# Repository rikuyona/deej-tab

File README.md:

# deej-tab

物理スライダーで、Windows / Mac のアプリごとの音量と **ブラウザ（Chrome・Edge など）のタブごとの音量** を操作する自作ミキサーです。
[deej](https://github.com/omriharel/deej) を元に、PC アプリ・ブラウザの拡張機能・LED 付きファームウェア・3D プリント用ケース（[MakerWorld](https://makerworld.com/models/3382344)）までまとめてあります。

<p align="center"><sub>完成イメージ（3D レンダリング）。スライダー 5 本・ノブ 1 つ、外形 126×126mm</sub></p>

- [できること](#できること) / [必要なもの](#必要なもの) / [セットアップ](#セットアップ) / [使い方](#使い方) / [困ったとき](#困ったとき) / [Mac 版について](#mac-版について) / [仕組み](#仕組み) / [開発](#開発)

## できること

- スライダー 5 本＋ノブ 1 つに、全体音量・マイク・アプリ（Discord・Spotify など）・**Chrome のタブ**・今使っているアプリ・ゲーム・OBS の音声ソースを割り当てる
- Chrome で開いた配信や動画を、タブごとに別のスライダーで調整（Alt+Shift+A でタブを割り当て）
- 日本語・英語の画面（English UI）
- 設定画面で割り当て・スライダーごとの最大音量（100% 超えも可。タブ・OBS のみ）・音量の変わり方を変更
- プロファイル（割り当て一式）の切り替え。アプリが前に来たら自動で切り替えも可
- 一時停止（ショートカットも可）。止めるとアプリの音量を元に戻す（全体の音量はそのまま）
- スライダーの LED で状態や音の大きさを表示。光り方は設定画面で選べる
- config.yaml は deej と互換

## 必要なもの

作り方は 2 通りあります。PC アプリ・拡張機能・ファームウェアはどちらも同じです。

| | 配線版 | 基板版 |
|---|---|---|
| 作り方 | スライダーごとに Nano まで線を引き回してハンダ付け | スライダー 5 本とノブを 1 枚の基板に載せ、Nano とはケーブル 3 本でつなぐ |
| 向いている人 | 基板を注文せず、部品だけで作りたい | 配線の手間を減らしたい（基板は JLCPCB などに注文） |
| 部品・作り方 | 下の [部品（配線版）](#部品配線版) と [配線（配線版）](#配線配線版) | 下の [部品（基板版）](#部品基板版) と [pcb/README.md](pcb/README.md) |
| ケース | [MakerWorld](https://makerworld.com/models/3382344) | [Releases](../../releases/tag/pcb-v0.1.0) の `deej-tab-pcb-0.1.0-case.zip`（[下](#4-ケースを印刷する任意)） |

### PC

- Windows 10 / 11、または macOS 14.2 以降の Apple シリコン（M1 以降）の Mac（Mac は [Mac 版について](#mac-版について) を参照）
- Chrome・Edge・Brave など Chromium のブラウザ（Chrome 116 相当以降。タブの音量を操作する場合）

### 部品（配線版）

| 部品 | 例 | 数 |
|---|---|---|
| マイコン | Arduino Nano 互換ボード（USB Type-C 版。ケースは Mini-USB の Nano には合いません） | 1 |
| スライダー | Bourns PTL60-15R0-103B2（60mm・10kΩ B カーブ・赤 LED 付き） | 5 |
| 回転ボリューム | 16mm 型 10kΩ B カーブ（SH16K4B103L20KCCI など。6mm ローレット軸 18 山・軸長 20mm・M7 取付ネジ・回り止め付き） | 1 |
| ノブ | 3D プリント（[MakerWorld](https://makerworld.com/models/3382344) のデータ）または市販の 6mm 軸用（ABS-28 など） | 1 |
| LED 用抵抗 | 180Ω〜1kΩ（1/4W・1/6W など。例：330Ω） | 5 |
| M2 皿ネジ | M2×4 程度（ケースにスライダーを固定。1 本につき 2 本） | 10 |

LED 用抵抗：スライダーの赤色 LED はデータシートで順方向電流 20mA・順方向電圧 1.8V（標準）と規定されているので、5V で 20mA 以下にするには (5V − 1.8V) ÷ 20mA ≒ 160Ω 以上が必要です。値が小さいほど明るくなります（330Ω で約 10mA）。

LED なしのスライダーでも動きます（LED の機能が使えないだけです）。

### 配線（配線版）

同じ名前の札どうしをつなぎます。5V と GND は全部の部品で共通なので、まとめて Nano の 5V・GND へつなぎます。

| 部品 | 端子 | つなぐ先 |
|---|---|---|
| スライダー 1〜5 | 1 | GND |
| | 3 | 5V |
| | 2（ワイパー） | A0〜A4 |
| | B（LED＋） | 抵抗 → D3 / D5 / D6 / D9 / D10 |
| | E（LED−） | GND |
| | L | つながない |
| 回転ボリューム | 両端 | 5V / GND |
| | 中央 | A5 |

D0 / D1 は USB シリアルに使うので空けておきます。

### 部品（基板版）

基板を発注・組み立てて、スライダー 5 本・ノブの値と LED が動くことを確かめてあります。部品はすべてスルーホールで、手でハンダ付けします。

| 部品 | 例 | 数 |
|---|---|---|
| 基板 | [Releases](../../releases) の `pcb-v0.1.0` のガーバーを JLCPCB などに注文（2 層・1.6mm・100×100mm 以内） | 1 |
| マイコン | Arduino Nano 互換ボード（USB Type-C 版） | 1 |
| スライダー | Bourns PTL60-15R0-103B2（配線版と同じ） | 5 |
| 回転ボリューム | 配線版と同じ SH16K4B103L20KCCI（端子の曲がりを伸ばして基板に挿す。[pcb/README.md](pcb/README.md#ボリュームの端子)） | 1 |
| LED 用抵抗 | 150Ω 1/4W | 5 |
| コンデンサー | 0.1µF（各スライダー・ノブのノイズ対策）・10µF（5V） | 6・1 |
| コネクター | JST ZH 横向き 3 ピン（S3B-ZR-3.4）1 個・6 ピン（S6B-ZR-3.4）2 個 | 3 |
| コード | ZH 相当のコネクター付きコード 3P 黒白赤（秋月 118272）1 本・6P(H)（秋月 105719）2 本 | 3 |
| M2 皿ネジ | M2×4（スライダーを天板に固定） | 10 |

型番・秋月の通販番号入りの一覧は `pcb-v0.1.0` の `deej-tab-pcb-0.1.0-bom.csv`、ケーブルの対応・組み立て・注文のしかたは [pcb/README.md](pcb/README.md) にあります。基板版は上の「配線（配線版）」の代わりに、pcb/README.md の「ケーブル」と「組み立て」を見てください。

## セットアップ

[Releases](../../releases) の最新版から、使う PC に合わせてダウンロードします。

| やること | Windows | Mac |
|---|---|---|
| [1. PC アプリを入れる](#1-pc-アプリを入れる) | `deej-tab-x.y.z-setup.exe` | `deej-tab-x.y.z-mac.dmg` |
| [2. ファームウェアを書き込む](#2-コントローラーにファームウェアを書き込む) | 設定画面から（ダウンロード不要） | 設定画面から（ダウンロード不要） |
| [3. ブラウザの拡張機能を入れる](#3-ブラウザの拡張機能を入れる)（タブの音量を変えるとき） | インストール済み（読み込むだけ） | `deej-tab-extension-x.y.z.zip` |
| [4. ケースを印刷する](#4-ケースを印刷する任意)（任意） | MakerWorld（基板版は `pcb-v0.1.0` の case.zip） | MakerWorld（基板版は `pcb-v0.1.0` の case.zip） |

うまくいかないときは [困ったとき](#困ったとき) を見てください。

### 1. PC アプリを入れる

**Windows**

1. `deej-tab-x.y.z-setup.exe` をダブルクリックする
   - 「Windows によって PC が保護されました」と出たら、「詳細情報」→「実行」を押す（コード署名をしていない個人の配布物なので出ます）
2. 「次へ」を押す（「Windows の起動時に自動で起動する」は初期設定でオン）
3. 最後に「完了」を押すと deej-tab が起動して、設定画面が開く

管理者の許可は要りません。`%LOCALAPPDATA%\Programs\deej-tab` に入り、スタートメニューに deej-tab が出ます。deej-tab は画面右下のタスクトレイに常駐します（アイコンは「^」の中に隠れていることがあります）。

**Mac**（Apple シリコン・macOS 14.2 以降）

1. `deej-tab-x.y.z-mac.dmg` を開き、`deej-tab.app` を隣の「Applications」へドラッグする。入れ終わったら、Finder のサイドバーの ⏏ で dmg を取り出す（dmg の中から起動しないでください。取り出すと消えます）
2. 初回は次の手順で起動する（Apple の公証を受けていないため、ダブルクリックだけでは開けません）
   - **最近の macOS（15 Sequoia 以降。26 Tahoe など）**：`deej-tab.app` をダブルクリックし、「開いていません」と出たら「完了」を押す。システム設定 →「プライバシーとセキュリティ」を開き、下のほうの「セキュリティ」に出ている deej-tab の行で「このまま開く」を押す（パスワードを聞かれたら入力）
   - **macOS 14 Sonoma**：`deej-tab.app` を右クリック →「開く」→ 出てきた画面で「開く」
3. アプリごとの音量を初めて変えたときに「システムオーディオの録音」の許可を求められるので、許可する（音を受け取って音量をかけ直すだけで、録音・保存はしません）

deej-tab はメニューバーに常駐し、アイコンから設定画面を開けます。

### 2. コントローラーにファームウェアを書き込む

初めて使う Nano には、deej-tab の設定画面からファームウェアを書き込みます（Arduino IDE は要りません）。書き込み済みのコントローラーなら、USB につなぐだけで自動で見つかるので、この手順は要りません。

1. Nano を USB で PC につなぐ
2. 設定画面の「設定」→「コントローラー」の「接続先」で、Nano のポートを選ぶ（Windows は `COM…`、Mac は `/dev/cu.usbserial-…`）
3. 「ファームウェア」の「書き込む」を押す。10〜20 秒で終わり、そのままつながる

- 書き込むまでは「コントローラーが見つかりません」と出ますが、そのままで大丈夫です
- 互換品に多い古いブートローダー（Old Bootloader）の Nano も、自動で見分けます
- 書き込み直しても、LED の光り方・スライダーの端の位置の設定は残ります。deej-tab を更新して新しい版のファームウェアが入ると、「ファームウェア」の行に「新しい版を書き込めます」と出ます
- ポートが一覧に出ないときは、[困ったとき](#困ったとき) の「コントローラーが見つからない」を見てください

<details>
<summary>Arduino IDE で書き込む場合</summary>

1. `deej-tab-firmware-x.y.z.zip` を展開する
2. [Arduino IDE](https://www.arduino.cc/en/software) で `firmware/deej-6ch-led/deej-6ch-led.ino` を開く
3. ボード「Arduino Nano」、ポートを選んで書き込む
   - 互換品で失敗する場合は、プロセッサを「ATmega328P (Old Bootloader)」にする
   - deej-tab が起動中だと書き込めません（トレイから終了してから）

</details>

### 3. ブラウザの拡張機能を入れる

タブごとに音量を変えるときに入れます。Chrome・Edge・Brave・Vivaldi など、Chrome と同じ仕組み（Chromium）のブラウザで使えます（Firefox・Safari は非対応）。

1. 拡張機能のフォルダを用意する
   - **Windows（インストーラー）**：`%LOCALAPPDATA%\Programs\deej-tab\extension`（インストールの完了画面の「ブラウザの拡張機能のフォルダを開く」でも開けます）
   - **Mac・zip 版**：`deej-tab-extension-x.y.z.zip` を展開する（展開したフォルダは消さずに残しておく）
2. ブラウザで `chrome://extensions`（Edge は `edge://extensions`）を開き、「デベロッパー モード」をオンにする（Chrome は右上、Edge は左のメニュー）
3. 「パッケージ化されていない拡張機能を読み込む」を押し、1 のフォルダを選ぶ

拡張機能は 1 つのブラウザにだけ入れてください（2 つのブラウザに入れると、タブの番号がぶつかります）。

### 4. ケースを印刷する（任意）

ケース・ツマミの 3D データは MakerWorld で配布しています。印刷設定と組み立て方もそちらにあります。

| 分解図 | スライダーのツマミ | 上から |
|---|---|---|
|  |  |  |
| 天板・底ケース・Arduino Nano 固定クリップの 3 部品＋ツマミ | 黒い外殻と白い芯の 2 色。LED の光で白い線が光ります | 目盛りと番号は彫り。塗料を流し込んで色を付けます |

**MakerWorld：** [deej-tab Volume Mixer (5 faders + knob, LED)](https://makerworld.com/models/3382344)

**基板版のケース**：天板の形が配線版と違う（スライダーをネジで留める・基板の裏の部品とハンダを逃がす）ので、MakerWorld の天板は使えません。[Releases](../../releases/tag/pcb-v0.1.0) の `deej-tab-pcb-0.1.0-case.zip` に、基板版の天板・底ケースと、ほかの部品の STL を入れてあります（中の README.txt に印刷の向きを書いてあります）。ツマミとノブは配線版と同じなので、2 色の組み合わせ済みデータは MakerWorld のものが使えます。配線版の底ケースを使うときは、四隅の柱に `spacer.stl`（厚さ 1.8mm の輪）を載せ、四隅を M3×10 で締めます。

寸法を変えたいときは `case/case.py` の先頭の設定を書き換えて作り直せます（[開発ガイド](docs/dev/README.md#ケースを作る)）。

### 更新・アンインストール

- **アプリから更新（1.5.0 から）**：新しい版が出ると、設定画面の上とタスクトレイのメニューに出ます。インストーラーで入れた Windows は「更新する」を押すと、新しい版を落として入れ直し、自動で起動し直します（設定はそのまま）。zip 版と Mac は、ダウンロードのページを開くので、下の手順で入れ直します。確かめるのは起動したときと 1 日 1 回で、「設定」→「アップデート」で止められます
- **Windows の更新**：新しい版の `setup.exe` を実行するだけです。動いている deej-tab は自動で終了し、設定はそのまま残ります
- **Mac の更新**：メニューバーから deej-tab を終了し、新しい dmg の `deej-tab.app` を「Applications」へドラッグして「置き換える」。初回と同じ起動の手順がもう一度必要になることがあります（録音の許可は残ります）
- **拡張機能の更新**：Windows（インストーラー）はフォルダの中身が自動で新しくなります。Mac・zip 版は新しい zip の中身でフォルダを置き換えます。どちらも、そのあと拡張機能のページで deej タブ音量の「再読み込み」（↻）を押します
- **アンインストール**：Windows は「設定」→「アプリ」から（設定ファイルとログは残します）。Mac は `deej-tab.app` をゴミ箱へ
- **インストールせずに使う（Windows）**：`deej-tab-x.y.z-windows.zip` を展開して `deej-tab.exe` を起動します（設定ファイルとログは exe の隣）。隣の `_internal` フォルダも deej-tab の一部なので、exe と一緒に置いてください（1.4.0 までは exe だけでした。更新する時は、終了してから中身を全部置き換えます）。zip 版からインストーラー版に移るときは、deej-tab を終了してから、zip 版の `config.yaml` を `%LOCALAPPDATA%\Programs\deej-tab` にコピーすると設定を引き継げます

## 使い方

deej-tab はタスクトレイに常駐します。アイコンをクリックすると設定画面が開きます。右クリックのメニューからは、一時停止・プロファイルの切り替え・自動起動のオン／オフ・終了ができます。

### ミキサー：スライダーに割り当てる

スライダー 1〜5 とノブのそれぞれに、操作したい音量を割り当てます。各スライダーの「＋ 割り当てを追加」から選び、1 本に複数を割り当てることもできます。メーターの塗りが今の音量、赤いつまみがスライダーの位置です。

選べるもの：

| 種類 | 内容 |
|---|---|
| 全体音量・システム音・マイク | Windows の音量 |
| 今使っているアプリ | いちばん手前のウィンドウのアプリ（ゲーム中ならゲーム） |
| ゲーム（全画面のアプリ） | 最後に全画面だったアプリ。ほかのウィンドウが前に来ても操作し続けます |
| そのほかのアプリ | どのスライダーにも割り当てていないアプリ全部 |
| Chrome タブ 1〜6 | 拡張機能で番号を付けたタブ（[下](#chrome-のタブの音量を操作する)） |
| アプリ | 音を出しているアプリ・起動中のアプリ・インストール済みのアプリから選べます。検索もできます |
| OBS の音声ソース | OBS 連携をオンにすると出ます |

同じ割り当て先は 1 本のスライダーにしか置けません（ほかのスライダーにあれば移動します）。

<br clear="right">

### スライダーごとの設定

各スライダーの右上のアイコンから、そのスライダーだけの設定を変えられます。

- **向きを反転**：上げると音が小さくなるときに
- **音量の変わり方**：スライダーを速く動かしたとき、音量がどのくらいかけて追いつくか
- **いちばん上まで上げたときの音量**：25〜400%。100% を超える分は Chrome のタブと OBS だけに効きます（Windows の音量は 100% が上限）
- **100% になる位置**：スライダーのどこで 100% になるか

<br clear="right">

### Chrome のタブの音量を操作する

1. 設定画面で、スライダーに「Chrome タブ 1」などを割り当てます
2. 音量を変えたいタブを開いて、**Alt+Shift+A** を押します。空いている番号に割り当てられ、ツールバーのアイコンに番号が出ます
   - もう一度押すと次の番号へ移り、最後は解除されます
   - **Alt+Shift+1・2** で番号を指定、ページの右クリック →「deej タブ音量」からも割り当て・解除できます（キーは `chrome://extensions/shortcuts` で変更できます）
3. 拡張機能のアイコン（**Alt+Shift+D**）を押すと、割り当ての一覧と今の音量が見られます。ほかのタブに割り当て済みの番号は、ここから入れ替えたり解除したりできます
4. ポップアップの「音が鳴ったタブを自動で割り当てる」をオンにすると、動画などの音が鳴り始めたタブが空いている番号に自動で割り当てられます（ポップアップでは番号の横に「自動」と出ます）。自動で割り当てたタブは「ページ内の動画の音量を変える」方式で調整します

ポップアップでは、番号ごとの今の音量（100% を超えるとオレンジ）と、割り当てたタブが見られます。

<br clear="right">

タブの音量は「Chrome のアプリ音量 × 全体音量」に対する割合です。音量の変え方は 2 種類あり、ポップアップで切り替えられます。

| 方式 | 内容 |
|---|---|
| タブの音をまとめて調整（初期設定） | タブの音声をキャプチャして音量をかけます。0 でしっかり無音になり、100% を超える音量にもできます |
| ページ内の動画の音量を変える | ページの動画・音声の音量を直接変えます。サイトによっては 0 でもかすかに聞こえます |

### プロファイル

割り当て一式に名前を付けて保存し、切り替えられます（ミキサーの上の「プロファイル」）。プロファイルごとに次のことができます。

- **自動で切り替え**：指定したアプリが前に来たら、そのプロファイルに切り替えます。アプリを終了すると元に戻ります
- **切り替えのショートカット**：キーを押して切り替えます

切り替えた直後は、スライダーが今の音量の位置を通るまで音量を変えません（音量が飛ばないように。設定でオフにできます）。

### 一時停止

設定画面の上の「スライダー操作」スイッチ、タスクトレイのメニュー、ショートカットで一時停止できます。一時停止中はスライダーを動かしても音量が変わりません。止めたときに、アプリ・マイク・OBS の音量を deej-tab が変える前に戻すこともできます（全体の音量は急に大きくならないよう、止めた時のまま）。

### 設定

設定画面の「設定」ページでは、次のものを変えられます。

- **言語**：自動（Windows の表示言語に合わせる）／日本語／English。タスクトレイのメニューと Chrome 拡張機能のポップアップ・右クリックメニューも切り替わります
- **コントローラー**：つなぐ COM ポート、全スライダーの向き、揺れの抑え、LED で知らせること、自動起動
- **LED の光り方**：操作していないとき・起動したとき・操作したときの光り方と明るさ。プレビューで確かめながら選べ、コントローラーに保存されるので PC から外しても同じ光り方になります
- **動作**：音量の変わり方、一時停止したら元に戻す、プロファイル切り替え時に音量を飛ばさない、一時停止のショートカット
- **OBS 連携**：obs-websocket で OBS の音声ソースを操作

#### スライダーの端の位置を合わせる

いちばん下・いちばん上まで動かしても 0% / 100% にならないときは、「コントローラー」→「スライダーの端の位置を合わせる」で各スライダーを端まで動かします。

設定は `deej-tab.exe` の隣の `config.yaml` に保存されます。手で書き換えても、保存すると自動で読み直します（形式は deej と互換）。

## 困ったとき

**コントローラーが見つからない（設定画面に「コントローラーが見つかりません」と出る）**

- USB ケーブルを差し直す。充電専用のケーブルでは通信できないので、データ通信できるケーブルを使う
- **Windows で、互換品の Nano がポートの一覧に出ない**：USB のドライバ（CH340）が入っていません。お知らせの「ドライバのページを開く」からドライバを入れて、USB を差し直します（デバイス マネージャーの「ほかのデバイス」に「USB2.0-Serial」などと出ていれば、これです）。Mac はドライバは要りません
- Arduino IDE（シリアルモニタ）などのほかのアプリがポートを使っていたら、閉じる
- まだファームウェアを書き込んでいない Nano なら、[2. ファームウェアを書き込む](#2-コントローラーにファームウェアを書き込む) へ
- それでもだめなら、「設定」→「コントローラー」の「接続先」でポートを選び直す

**ファームウェアの書き込みに失敗する**

- 「接続先」のポートが Nano のものか確かめる（Nano を抜くと一覧から消えるポートが Nano です）
- Arduino IDE などのほかのアプリを閉じ、USB ハブを使っていれば PC に直接つないで、もう一度「書き込む」を押す（途中で失敗しても、もう一度書き込めば直ります）

**スライダーを動かしても音量が変わらない**

- 設定画面の上の「スライダー操作」がオンか（一時停止中は、上に「一時停止中です」と出ます）
- そのスライダーに割り当てがあるか。割り当てたアプリが音を出していないと、音量が変わらないことがあります
- タスクトレイ（Mac はメニューバー）のアイコンのつまみが灰色なら、コントローラーにつながっていません（上の「見つからない」へ）

**音量が 0% / 100% にならない・触っていないのに小刻みに変わる・向きが逆**

- 0% / 100% にならない：「設定」→「コントローラー」→「スライダーの端の位置を合わせる」
- 小刻みに変わる：「設定」→「コントローラー」→「揺れの抑え」を強くする
- 動かしたスライダーにつられて、触っていないスライダーまで揺れる（基板版で起きやすい）：ファームウェアを 1.3.3 以降にする（「設定」→「コントローラー」→「ファームウェア」の「書き込む」）
- 上げると小さくなる：「設定」→「コントローラー」→「すべてのスライダーの向きを反転」（1 本だけなら、そのスライダーの ⚙ から）

**ブラウザのタブの音量が変わらない**

- 設定画面の上の「Chrome 拡張」が「接続中」か。「未接続」なら、deej-tab が動いているか確かめ、拡張機能のページで deej タブ音量の「再読み込み」（↻）を押す
- タブに番号を割り当てたか（ツールバーのアイコンに番号が出ます）。`chrome://` のページやウェブストアは割り当てられません
- 拡張機能は 1 つのブラウザにだけ入れる

**Mac でアプリの音が消えた**

- 「システムオーディオの録音」を許可していません。システム設定 →「プライバシーとセキュリティ」→「画面とシステムオーディオの録音」で deej-tab をオンにします

**それでも直らないとき**

ログ（`deej-tab.log`）を見ると原因がわかることがあります。Windows はインストール先（`%LOCALAPPDATA%\Programs\deej-tab`。zip 版は exe の隣）、Mac は `~/Library/Application Support/deej-tab/` にあります。

## Mac 版について

Apple シリコン（M1 以降）・macOS 14.2 以降の Mac 用です。Intel の Mac では動きません。入れ方は [1. PC アプリを入れる](#1-pc-アプリを入れる) にあります。CH340 のドライバは macOS に入っているので、互換品の Nano も USB につなぐだけで認識されます。

設定ファイルとログは `~/Library/Application Support/deej-tab/` に作られます。

### Windows 版との違い

- アプリは `.app` の名前で割り当てます（例：`discord.app`、`google chrome.app`）
- アプリごとの音量は macOS の Process Tap で、アプリの音を受け取って音量をかけ直して出力します。100% のアプリは何もしません
  - 音量を下げているアプリは、アプリ側で別の出力先を選んでいても Mac の出力先（システム設定のサウンド）から出ます
  - ごくわずかに音が遅れます（数十ミリ秒）
- 「システム音」には割り当てられません（Mac に通知音だけの音量がないため）
- LED を音に合わせるとき、マイクの音の大きさは表示しません（マイクの許可が必要になるため）
- ショートカットの Win は Command（⌘）、Alt は Option（⌥）です
- もう一度 `deej-tab.app` を開いても設定画面は出ません。メニューバーのアイコンから開いてください

## 仕組み

```
Nano ──USB シリアル──▶ deej-tab.exe ──Windows の音量 API──▶ アプリの音量
                       (Mac: deej-tab.app ──補助プログラム (Core Audio の Process Tap)──▶ アプリの音量)
 (スライダーの値)          │  ▲
                          │  └─ 設定画面 (http://127.0.0.1:8765/)
                          └─WebSocket──▶ Chrome 拡張機能 ──▶ タブの音量
```

拡張機能はタブの音声をキャプチャしてゲインをかけます。音量・設定のやりとりは PC の中（127.0.0.1）だけです。外とつながるのは、新しい版を確かめるとき（起動したときと 1 日 1 回、GitHub の公開されている版の一覧を読むだけ。「設定」→「アップデート」で止められます）と、更新するときのダウンロードだけです。

## 開発

ソースから動かす・exe や Mac 版を作る・ファームウェアを書き込む手順と、設計の資料は [開発ガイド](docs/dev/README.md) にまとめています。

## ライセンス

MIT License（[LICENSE](LICENSE)）。ファームウェアと config.yaml の形式は [deej](https://github.com/omriharel/deej)（MIT License, © Omri Harel）を元にしています。

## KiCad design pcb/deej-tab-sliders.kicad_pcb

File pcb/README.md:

# スライダー基板（基板版）

スライダー 5 本とノブを 1 枚の基板に載せ、Nano とはケーブル 3 本（JST ZH の電源 3 ピン・LED 6 ピン・信号 6 ピン）でつなぐ版です。
配線版（スライダーごとに線を引き回す）の改良版で、Nano・USB-C の位置とファームウェアはそのまま使えます。
部品はすべてスルーホールで、手でハンダ付けします（JLCPCB には基板だけを頼む）。

> **実物で確認済みです（2026-10-08）。** 発注した基板を組み立てて、スライダー 5 本・ノブの値と LED 5 個が動くこと、天板・基板・部品が合うことを確かめました。ノブのボリュームは、**配線版と同じ SH16K4 の端子の曲がりを伸ばして使います**（基板用として選んだ JH16K6 は、端子が v0.1.0 の長穴に最後まで入らなかった。下の「ボリュームの端子」）。ガーバーは Releases の `pcb-v0.1.0` にもあります。

- 基板：`deej-tab-sliders.kicad_pcb`（KiCad 10 で開ける）
- 作り直し：`"%LOCALAPPDATA%\Programs\KiCad\10.0\bin\python.exe" make_pcb.py`
  - 部品の配置と信号の割り当てはスクリプトで決め、線は自動配線（Freerouting 2.4.1）に引かせる（30 秒ほど）。GND は自動配線から外し、表裏のベタでつなぐ
  - 要るもの（`%LOCALAPPDATA%\deej-tab\tools`）：`freerouting-2.4.1.jar` と、Java 25 の zip 版（Eclipse Temurin JRE 25 を展開した `jdk-25...-jre`）。インストールは不要
  - `out/deej-tab-sliders-gerber.zip`：JLCPCB に出すガーバー一式
  - `out/deej-tab-sliders-bom.csv`：買う部品の一覧
  - `out/drc.txt`：KiCad の DRC の結果（エラー 0。残りは自作の部品形状がライブラリにない旨の警告だけ）
  - `out/deej-tab-sliders-top.svg` / `-bottom.svg`：表・裏の図
  - `outline.json`：基板の外形・コネクターと部品の位置（`case.py --pcb` が読む）
- ケース：`case\.venv\Scripts\python case\case.py --pcb` → `case/out/pcb/`
  - 配線版の底ケースを持っていれば、刷り直さずに使える。基板版の天板は 1.8mm 薄いので、四隅の柱に `spacer.stl`（厚さ 1.8mm の輪 4 個）を載せる。四隅を M3 で締めるなら M3×10

## 基板の中身

| 部品 | 型番 | 数 | 置き場所 |
|---|---|---|---|
| スライダー | Bourns PTL60-15R0-103B2（今と同じ） | 5 | 表（ハンダは裏） |
| ノブのボリューム | **SH16K4B103L20KCCI**（配線版と同じ。10kΩB。端子の曲がりを伸ばして長穴に挿す） | 1 | 表（パネルにナットで留める） |
| LED の抵抗 | カーボン抵抗 1/4W **150Ω**（足の間隔 10.16mm で寝かせる） | 5 | 裏（ハンダは表）。スライダーのすき間 |
| ノイズ対策 | 積層セラミックコンデンサー 0.1µF 50V **RD15F104Z1HL2L**（秋月 104065、10 個入り）各摺動子と GND の間 | 6 | 裏（ハンダは表） |
| 5V | 積層セラミックコンデンサー 10µF 25V **THD30E-1E106Z**（秋月 100464、足の間隔 5mm） | 1 | 裏（ハンダは表） |
| Nano へのコネクター | JST ZH 横向き **S3B-ZR-3.4**（JP）と **S6B-ZR-3.4**（JL・JA）（1.5mm、秋月） | 1＋2 | 裏（ハンダは表） |

- **LED の抵抗 150Ω**：赤 LED（Vf 1.8V、データシートの条件 20mA）に約 19mA。配線版の 330Ω（約 8.5mA）の約 2.2 倍の明るさ。5 個で約 95mA で、Nano（1 ピン 20mA 推奨）の範囲。これより下げると LED の 20mA を超える
- 基板の表はスライダー本体と天板（すき間 0.5mm）でふさがるので、抵抗・コンデンサー・コネクターの本体は裏に置き、表に出るハンダは天板の裏を 3mm 彫って逃がしている
- 基板：2 層・1.6mm・外形 100×100mm 以内（JLCPCB の最安枠）。Nano の真上は切り欠いてあり、Nano にハンダ付けする線の邪魔をしない
- ボリュームは今と同じくナットでパネルに留める（パネルの穴・回り止め・印刷のノブ・目盛りは配線版と同じ）。本体は取付面から 9.3mm とスライダー（7.0mm）より深いので、基板の左奥を切り欠いて本体を通す。端子を軸と平行に後ろへ伸ばし、基板の**長穴**（3.3×0.9mm）に通してハンダ付けする（SH16K4 は端子の V 字の曲がりを伸ばす。[ボリュームの端子](#ボリュームの端子)）
- 配線：自動配線（信号は主に裏、表はほぼベタ GND）。表裏ともベタ GND
- スライダーは今と同じ位置（22mm 間隔、ケースの X = 19 / 41 / 63 / 85 / 107）。端子は 4 本の列を手前にして上から見て左から 2・1・L・E（実物で確認済み）。ノブも同じ位置（19, 106）

## ケーブル（JP・JL・JA → Nano）

電源・LED・信号で 3 本に分けている。秋月のコネクター付コード（ZH 相当、片側ハンダメッキ）をそのまま挿し、ハンダメッキの側を Nano に付ける。1 番は四角いパッド。

- **JL（LED）と JA（信号）は Nano のすぐ左に縦に並び、口は Nano 向き（右）**。端子の並びは Nano の端子と同じ前後の順なので、コードはまっすぐ右へ出して、そのまま隣の Nano の端子に付けられる。1 番は奥の端
- **JP（電源）はボリュームの近く、口は手前**。コードは基板の下を手前へ出して、Nano の手前の端の 5V・GND へ

| コネクター | コード | 番号 | 信号 | Nano の端子 |
|---|---|---|---|---|
| JP 電源（3 ピン） | 3P 黒白赤（秋月 118272） | 1 | GND | GND（D 側） |
| | | 2 | +5V | 5V（A 側） |
| | | 3 | GND（予備） | 付けなくてよい |
| JL LED（6 ピン） | 6P(H) 白赤黒青黄緑（秋月 105719） | 1（奥） | D10 | D10（スライダー 5 の LED） |
| | | 2 | D9 | D9（スライダー 4） |
| | | 3 | D6 | D6（スライダー 3） |
| | | 4 | D5 | D5（スライダー 2） |
| | | 5 | D3 | D3（スライダー 1） |
| | | 6（手前） | 空き | 付けない |
| JA 信号（6 ピン） | 6P(H) 白赤黒青黄緑（秋月 105719） | 1（奥） | A0 | A0（スライダー 1） |
| | | 2 | A1 | A1（スライダー 2） |
| | | 3 | A2 | A2（スライダー 3） |
| | | 4 | A3 | A3（スライダー 4） |
| | | 5 | A4 | A4（スライダー 5） |
| | | 6（手前） | A5 | A5（ノブ） |

- JA のコードは Nano の A 側（A0 が奥、A5 が手前）、JL のコードは D 側の D10・D9・D6・D5・D3 に、それぞれ真横へ付ける
- **コードの色と番号の対応は、Nano に付ける前に確かめる**（基板に挿して、テスターで基板の端子とコードの先の導通を見る）。コネクターは向きが決まっているので挿し間違いはない。1 番の位置はデータシートの図から読んだもの
- コードは 20cm あるので、Nano までの長さに切ってから付ける（JA・JL は数 cm、JP は 10cm ほど）
- ファームウェア・アプリは今のまま（ピンの割り当ては配線版と同じ）

## 組み立て

1. 抵抗・コンデンサー・JP・JL・JA を**裏から挿して表でハンダ付け**し、表に出た足は短く切る
   - コンデンサーは基板に押し付けて付ける（裏の部品と底ケースの床のすき間はいちばん狭い所で約 2mm）
   - 抵抗は寝かせて付ける
2. ボリューム（SH16K4）の 3 本の端子の V 字の曲がりをラジオペンチで伸ばし、まっすぐ後ろ（軸と平行）へ向ける。3 本の間隔（5mm）がそろうようにする
3. 天板に、スライダーを表から M2 皿ネジ（**M2×4、10 本**）で、ボリュームをナットで留める。基板版は本体の下に基板があるので、配線版の爪はない
4. 基板を裏からかぶせる（スライダーの端子とボリュームの 3 本の端子が穴に入る。入りにくいときはボリュームの端子の向きを少し直す）
5. 裏からスライダーとボリュームをハンダ付けする（パネルに合った位置で固まる）。ボリュームの端子が長く出たら、ハンダのあと短く切る
6. コードを JP・JL・JA に挿し、Nano へ。天板を底ケースに閉じる
   - コネクターは奥まで挿す。半挿しになりやすく、半挿しだとスライダーの値がおかしくなる

## ボリュームの端子

基板は、ボリュームの取付面（パネルの裏）から 7.0〜8.6mm 後ろにあります（スライダーの高さで決まる）。ボリュームの端子は、ここまで軸と平行に伸びて、長穴（3.3×0.9mm、`make_pcb.py` の `POT_SLOT`）を通る必要があります。寸法はデータシート（秋月の PDF）の図の線の座標から測りました。

### SH16K4B103L20KCCI（使う方）

- 端子は本体の前寄りから外へ出て、V 字に折り返して後ろへ伸びるはんだ付け用の板。先は幅 3.0mm・穴 1.5mm、根元は幅 1.6mm、厚さ 0.49mm、軸の中心から約 12.7mm
- 曲げたままだと先は取付面の約 6.3mm 後ろまでで、基板（7.0mm）に届かない。**V 字の曲がりを伸ばしてまっすぐにすると、先は約 10.9mm 後ろまで届き、基板を貫通して裏に約 2mm 出る**。長穴を通るのは先の幅 3.0mm・厚さ 0.49mm の所で、すっと入る（実物で確認）
- 配線版と同じ部品なので、パネルの穴・回り止め・ノブはそのまま

### JH16K6B103L20KC-H13（基板用。最初に選んだ方）

- データシート（秋月の `JH16K6B103L20KC-H13.pdf`、縮尺 2:1 の図の線から測った）：端子は軸の中心から 13mm・5mm 間隔で、取付面の 3.5〜13.3mm 後ろまで軸と平行に伸びる板。**幅 3.0mm・厚さ 0.5mm**、本体より後ろの先 4.0mm だけ細い（基板に挿す時用の Ø1.2 の穴に合う太さ）。寸法の書いていない所の公差は「10 以下 ±0.3・10〜100 ±0.5」なので、幅は最大 3.3mm、軸からの距離は 13±0.5mm になり得る
- 基板（取付面の 7.0〜8.6mm 後ろ）は、幅の広い所を通る。基板の位置はスライダーの高さで決まるので、ケースの側では合っている（切る前の端子の先から底ケースの床まで約 7mm）
- **v0.1.0 の長穴 3.3×0.9mm（`make_pcb.py` の `POT_SLOT`）は狭い**：めっきで 0.1mm 前後細くなるので、幅 3.0mm（公差で 3.3mm）の板は入らないことがある。実物では先の細い所だけ入り、幅の広い所で止まった
  - v0.1.0 の基板で組む時：端子の幅の広い所のうち、本体の後ろの面から手前 3mm ほど（基板が通る所。取付面の 6.3〜9.3mm 後ろ）を、ニッパーかやすりで 2.8mm くらいまで細くしてから挿す
  - 直すなら：長穴を 4.0×1.2mm ほどに広げる（幅 3.3＋間隔の公差、厚さ 0.5＋軸からの距離の公差に、めっきの分を足す）。奥の端子のパッドが基板の奥の縁に近いので、パッドの大きさと外形の見直しも要る

## JLCPCB への注文

1. `out/deej-tab-sliders-gerber.zip` をアップロード（2 層・1.6mm・その他は初期設定のまま）
2. 部品実装（PCB Assembly）は使わない（部品はすべて手でハンダ付け）

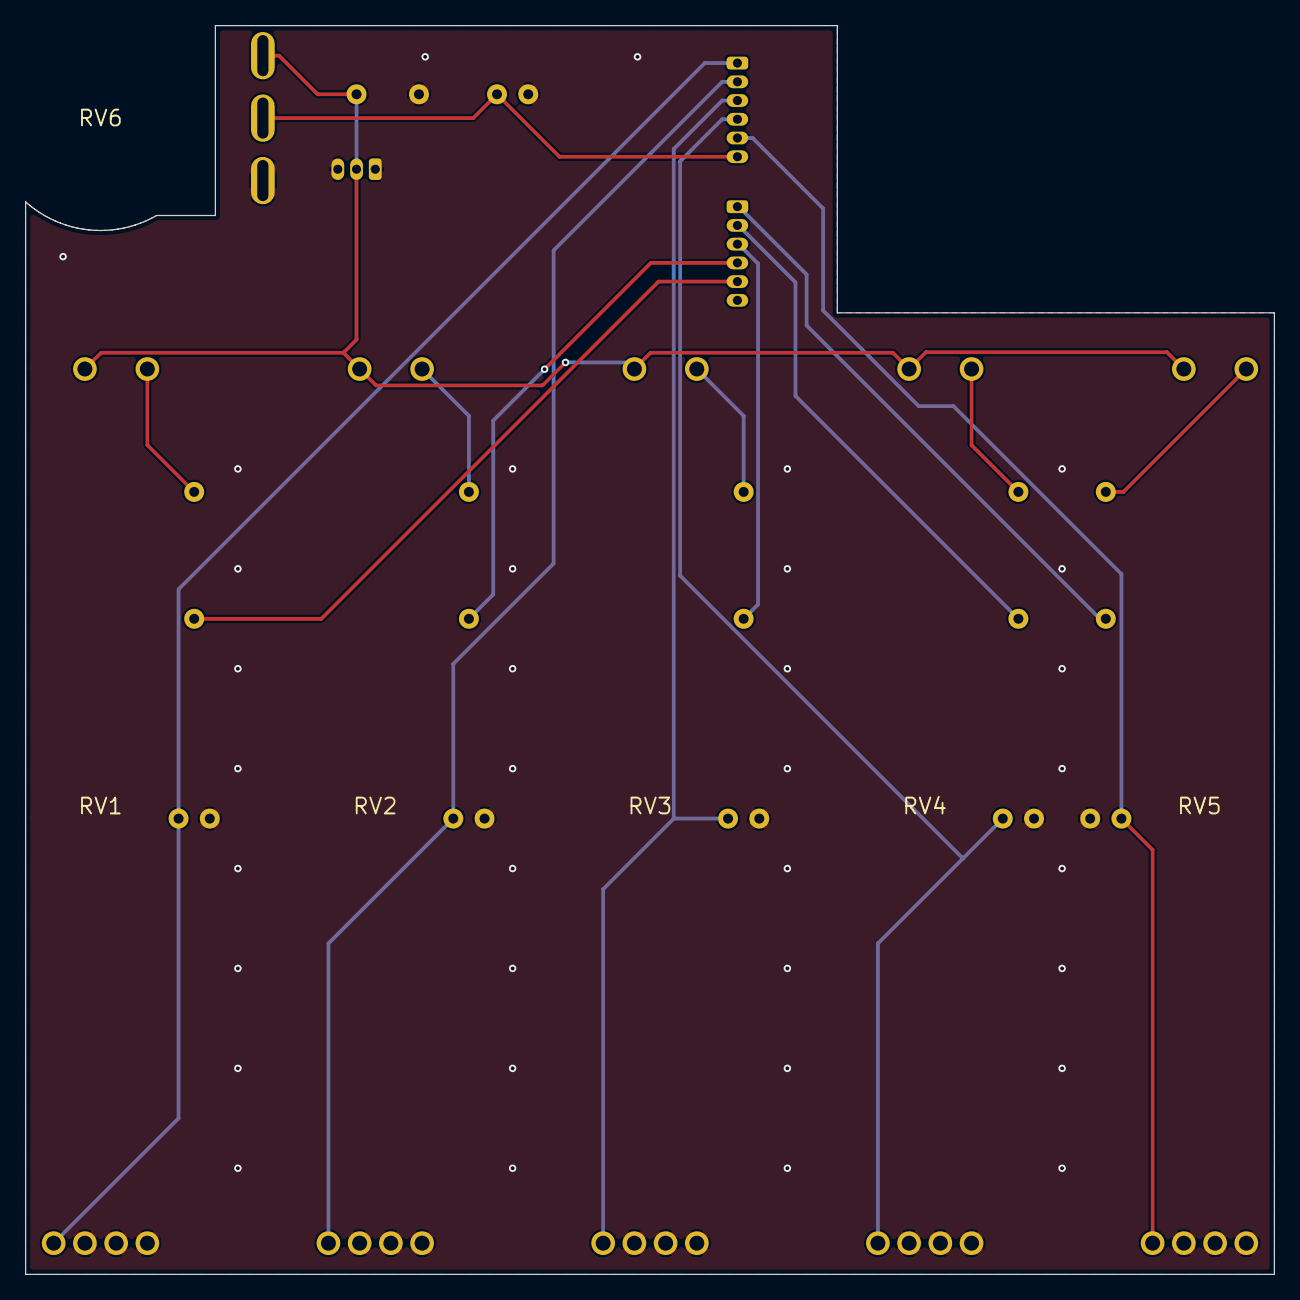
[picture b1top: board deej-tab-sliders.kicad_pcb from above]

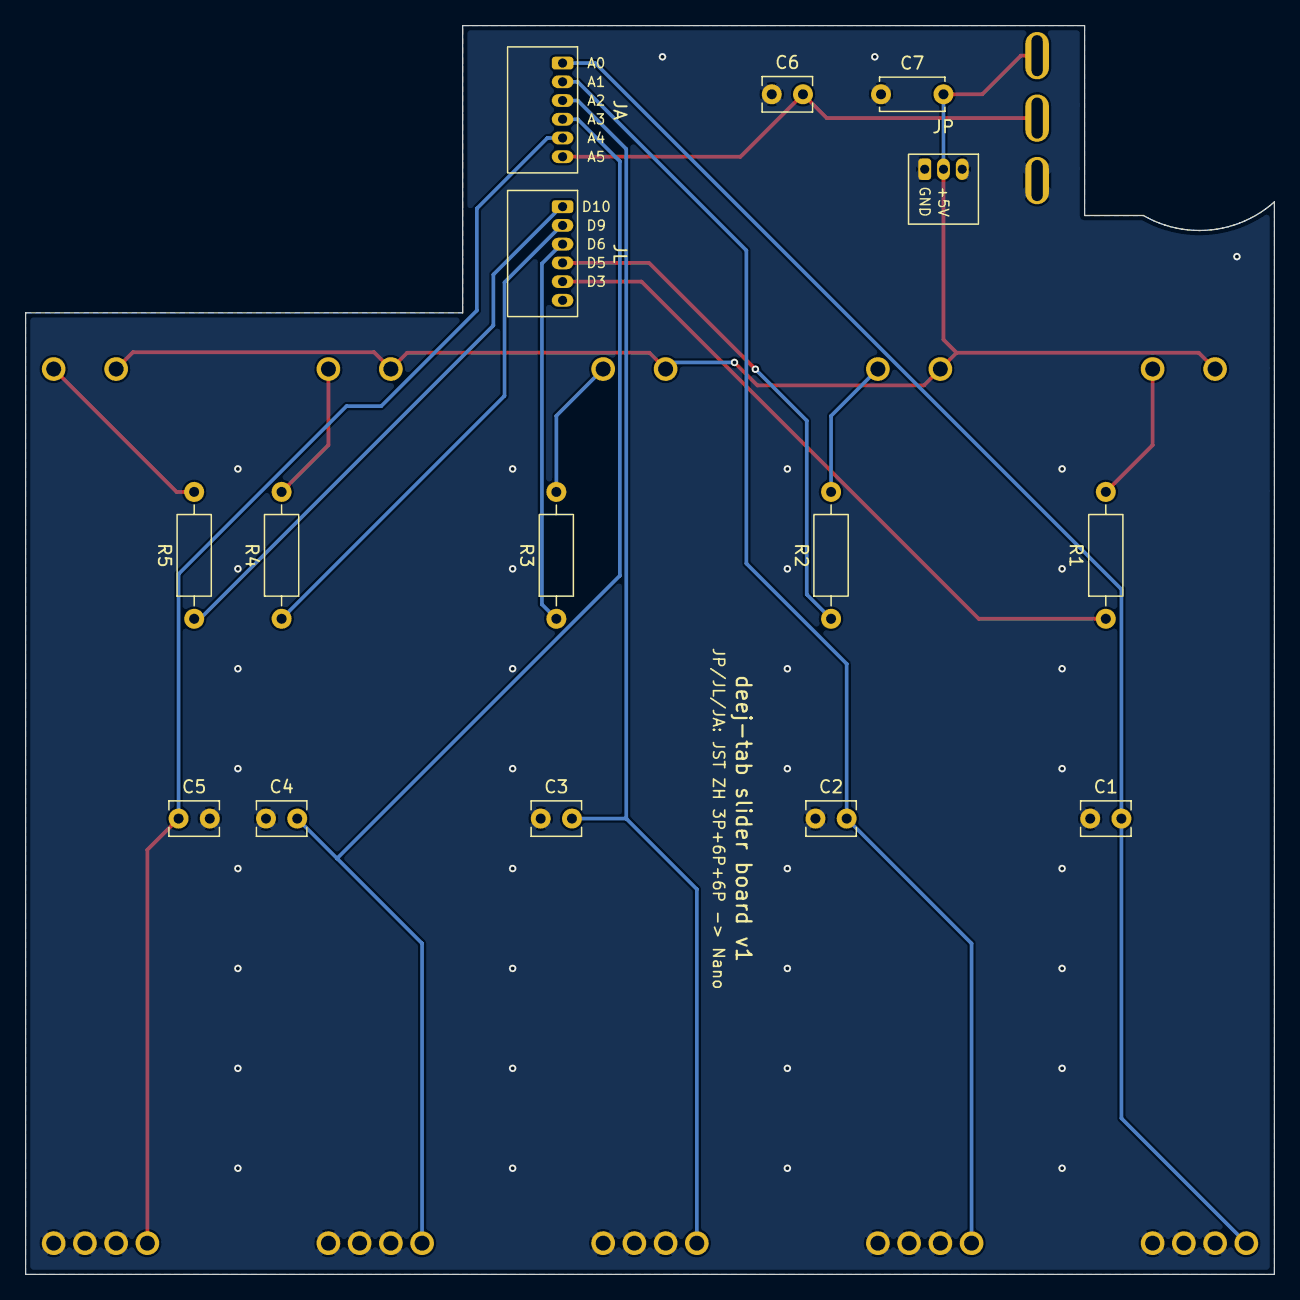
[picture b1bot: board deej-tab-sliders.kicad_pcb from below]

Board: 2 copper layers, 100.0 x 100.0 mm, 21 parts (12 on the bottom side), 18 nets.

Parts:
C1, C2, C3, C4, C5, C6: 100nF; C_Disc_D3.8mm_W2.6mm_P2.50mm
C7: 10uF; C_Disc_D5.0mm_W2.5mm_P5.00mm
JA: S6B-ZR; JST_ZH_S6B-ZR_Horizontal
JL: S6B-ZR; JST_ZH_S6B-ZR_Horizontal
JP: S3B-ZR; JST_ZH_S3B-ZR_Horizontal
R1, R2, R3, R4, R5: 150; R_Axial_DIN0207_L6.3mm_D2.5mm_P10.16mm_Horizontal
RV1, RV2, RV3, RV4, RV5: PTL60-15R0-103B2; Bourns_PTL60
RV6: JH16K6B103L20KC-H13; Supertech_JH16K6_H13_slots

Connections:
+5V: C7.2, JP.2, RV1.3, RV2.3, RV3.3, RV4.3, RV5.3, RV6.3
A0: C1.2, JA.1, RV1.2
A1: C2.2, JA.2, RV2.2
A2: C3.2, JA.3, RV3.2
A3: C4.2, JA.4, RV4.2
A4: C5.1, JA.5, RV5.2
A5: C6.2, JA.6, RV6.2
D3: JL.5, R1.1
D5: JL.4, R2.1
D6: JL.3, R3.1
D9: JL.2, R4.1
D10: JL.1, R5.1
GND: C1.1, C2.1, C3.1, C4.1, C5.2, C6.1, C7.1, JP.1, JP.3, RV1.1, RV1.E, RV1.L, RV2.1, RV2.E, RV2.L, RV3.1, RV3.E, RV3.L, RV4.1, RV4.E, RV4.L, RV5.1, RV5.E, RV5.L, RV6.1
LED1: R1.2, RV1.B
LED2: R2.2, RV2.B
LED3: R3.2, RV3.B
LED4: R4.2, RV4.B
LED5: R5.2, RV5.B
